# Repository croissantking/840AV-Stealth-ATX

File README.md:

$\color{#FF0000}{IMPORTANT!}$ <b>Working with switching power supplies involves dangerous, potentially lethal voltages, even when the device is disconnected from mains power. Improper handling can result in serious injury or death.

This repository provides Gerber files and related materials in good faith to the Macintosh hobby community, without any warranty or guarantee of any kind, including safety, reliability, or fitness for any particular purpose.

This design has not been safety-certified or fully validated under all operating conditions.

By using this material, you explicitly agree that:

- You assume all risk and responsibility for construction, modification, and use
- The author is not liable for any damage, injury, or death resulting from use or misuse
- You will only proceed if you are qualified and understand high-voltage electronics safety

If you are not experienced with mains-powered or high-voltage electronics, do not attempt to use this material.</b>

<b>Introduction and Outline</b>
-
This two-layer 'ATX Conversion Board' PCB enables you rebuild a failed Delta SMP-220DB Power Supply, found in your Apple Macintosh Quadra 800/840AV or Power Macintosh 8100, with easily obtainable second hand parts.

The PCB replicates the exact dimensions of the Delta's lower PCB, securing to the chassis just as the original. It's designed to have the internals of one of the following Seasonic-based ATX power supplies stood off above it as a mezzanine board:

- Antec EarthWatts EA-380 / EA-430 / EA-500 (without 'D' suffix)
- Seasonic SS-350ET / SS-400ET / SS-500ET (ES suffix also OK)
- Seasonic S12-II 500W

The PCBs in these PSUs are all the same and are labelled ATX400W REV:A5. Some of the components may be slightly different based on the output rating.

If you want, you can modify the Gerbers to fit the mounting locations of your own chosen PSU. You can also drill holes into the board but note that a new connection should be made to the ground plane from each of the new standoff locations if doing this.

The design reuses the Delta SMP-220DB AC inlet board, and replicates both the original monitor passthrough power relay and fan speed control logic for authentic behaviour.

The 20/24 pin ATX harness is intended to be cut short and looped into the +12V, GND, -12V, +5V, PS_ON and +5VSB vias seen at the top of the new PCB. This is so a soft power inverter can be integrated, and also allows the original modular Mac PSU connector to be fitted in its original location.

BOM
-
Please see <a href="https://github.com/croissantking/840AV-Stealth-ATX/blob/main/BOM.csv" target="_blank" rel="noopener noreferrer">BOM.csv</a> for a parts list.

A Digikey cart is available here: https://www.digikey.co.uk/en/mylists/list/5MLRWHWYBX

Ordering
-
Simply download the Gerbers.zip file and then upload this to JLCPCB. Pick and Place files are available for the SMD parts, if desired.

Assembly
-
Here are the steps needed to assemble your rebuilt power supply. Note that I'm working with a slightly different pre-release board layout.

Once you have the bare Conversion Board PCB in your hands, decide if you'll be populating the fan circuit and the CRT relay as shown in the key above. Both circuits are optional. If you are not populating the fan control circuit then your fan should be connected to the ATX PCB. The through hole parts should be taken from the original Delta PSU (apart from the fan header), while SMDs should be newly obtained.

To install the AC inlet connector, either re-use the one from the original PSU or purchase a new one.

In this corner you'll install the 22-way MiniFit Jr Connector (you can bring this from the old board or purchase new), trimming off the mounting flange on one side in order to make way for a metal standoff. You'll also install a small capacitor and inverter for the soft power circuit.

Detach this little washer-type part from the original PCB and solder it here.

Now that the Conversion Board is populated you can fit the 4x standoffs. Place the ATX PCB on top and loosely screw it down with just the two standoffs marked '1' and '2' nearest the lower edge.

From the other side, you can start to trim the wires of your 20/24-pin ATX connector harness to the correct length to connect to the lower PCB. +12V, GND, -12V, +5V, PS_ON and +5VSB are needed; the rest can be shortened and insulated or desoldered as you wish. Hinge the ATX PCB upwards in order to get better access to solder.

You should cut back and insulate (or desolder) any drive connectors you don't need; the remaining ones will feed through the Delta housing circular cutout.

Here, all the connections have been successfully made, and the ATX PCB has been fully screwed down. 

Turn the assembly around again, and solder two short wires (live and neutral) from the Conversion Board to the ATX PCB. These should be at least 18AWG and preferably 16AWG.

The full assembly can now be installed in your Delta housing, and the AC inlet board plugged in to the Conversion Board.

$\color{#FF0000}{IMPORTANT!}$ The two large left-hand heatsinks on the ATX board have a high voltage when the unit is powered up (and for some time after power is disconnected) which will give you a nasty shock if you touch them. Please be extra careful.

Make sure to insulate the ferrite ring with kapton tape (or similar) so that it does not accidentally short out the exposed solder joints on the back of the inlet board.

You can re-use the original 120mm fan or install a modern replacement (e.g. Noctua). In my build I opted to re-use the original but it needed a longer cable with a three-pin connector for my Conversion Board's new header. So I peeled back the sticker over the motor to expose the solder points and replace the cable.

The cable was now long enough to reach the new header on the Conversion Board, with plenty of slack for ease of installation.

Here is the PSU fully assembled and ready to use.

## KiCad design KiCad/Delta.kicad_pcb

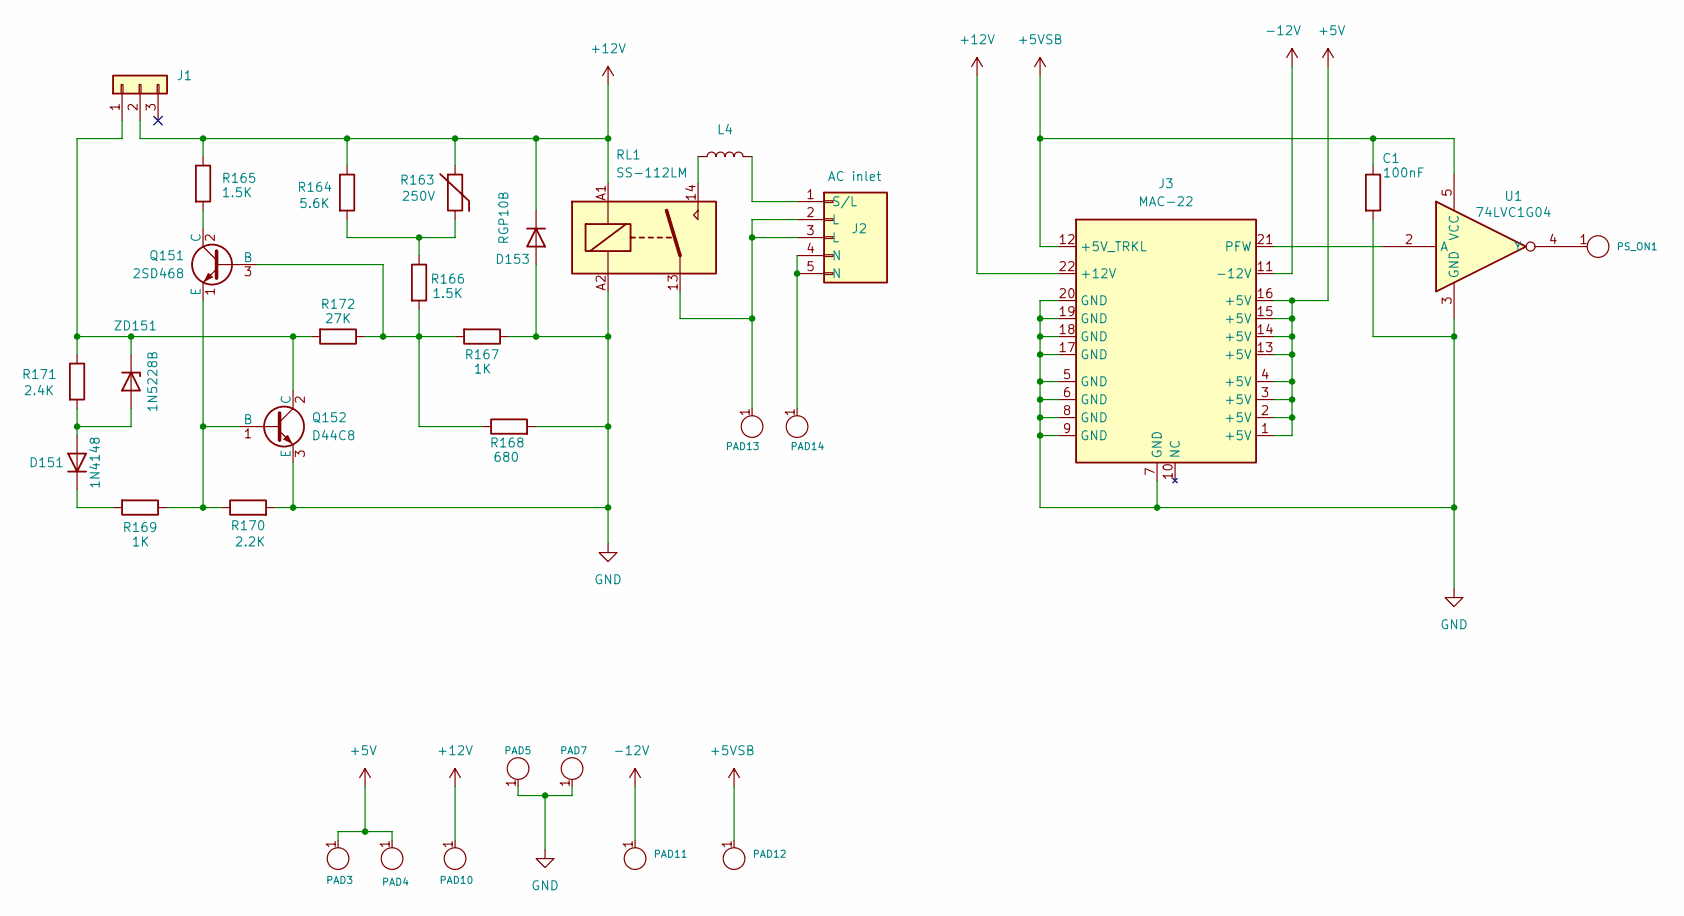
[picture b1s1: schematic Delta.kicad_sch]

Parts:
C1: 100nF; C_0805_2012Metric; LCSC C49678
D151: D_SOD-123; LCSC C83528
D153: D_DO-41_SOD81_P10.16mm_Horizontal
J1: Conn_01x03; FanPinHeader_1x03_P2.54mm_Vertical
J2: Conn_01x05; Pete_840AV_1x05_P4.00mm_Horizontal
J3: MAC-22; Molex_Mini-Fit_Jr_5569-22A1_2x11_P4.20mm_Horizontal_PETER
L4: L; L_Radial_L8.0mm_W8.0mm_P5.00mm_Neosid_SD8_PETER
PAD3, PAD4, PAD5, PAD7: SinglePad_PSU_Peter
PAD10: SinglePad_PSU_Peter_6_+12V
PAD11, PAD12: SinglePad_PSU_Peter_3_5VSB_-12V_PSON
PAD13, PAD14: SinglePad_PSU_Peter_1
PS_ON1: SinglePad_PSU_Peter_3_5VSB_-12V_PSON
Q151: 2SD468; TO-92_Inline_W4.0mm_Horizontal_FlatSideDown_PETER
Q152: D44C8; TO-220-3_Horizontal_TabDown
R163: 250V; RV_Disc_D7mm_W3.4mm_P5mm
R164: 5.6K; R_0805_2012Metric; LCSC C114538
R165, R166: 1.5K; R_0805_2012Metric; LCSC C114555
R167, R169: 1K; R_0805_2012Metric; LCSC C95781
R168: 680; R_0805_2012Metric; LCSC C93658
R170: 2.2K; R_0805_2012Metric; LCSC C114237
R171: 2.4K; R_0805_2012Metric; LCSC C114236
R172: 27K; R_0805_2012Metric; LCSC C114533
RL1: SS-112LM; Relay_SPST_Omron_G2RL-1A
U1: 74LVC1G04; SOT-23-5; LCSC C7827
ZD151: D_DO-35_SOD27_P10.16mm_Horizontal

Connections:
+5V: J3.1 (+5V), J3.2 (+5V), J3.3 (+5V), J3.4 (+5V), J3.13 (+5V), J3.14 (+5V), J3.15 (+5V), J3.16 (+5V), PAD3.1, PAD4.1
+5VSB: C1.1, J3.12 (+5V_TRKL), PAD12.1, U1.5 (VCC)
+12V: D153.1 (K), J1.2, J3.22 (+12V), PAD10.1, R163.1, R164.1, R165.1, RL1.A1
-12V: J3.11 (-12V), PAD11.1
GND: C1.2, D153.2 (A), J3.5 (GND), J3.6 (GND), J3.7 (GND), J3.8 (GND), J3.9 (GND), J3.17 (GND), J3.18 (GND), J3.19 (GND), J3.20 (GND), PAD5.1, PAD7.1, Q152.3 (E), R167.1, R168.2, R170.2, RL1.A2, U1.3 (GND)
unnamed: D151.2 (A), R171.2, ZD151.2 (A)
unnamed: D151.1 (K), R169.2
unnamed: J1.1, Q152.2 (C), R171.1, R172.2, ZD151.1 (K)
unnamed: J2.1 (CRT_L), L4.2
unnamed: J2.2 (L), J2.3 (L), PAD13.1, RL1.13
unnamed: J2.4 (N), J2.5 (N), PAD14.1
unnamed: J3.21 (PFW), U1.2 (A)
unnamed: L4.1, RL1.14
unnamed: Q151.3 (B), R166.2, R167.2, R168.1, R172.1
unnamed: Q151.2 (C), R165.2
unnamed: Q151.1 (E), Q152.1 (B), R169.1, R170.1
unnamed: R163.2, R164.2, R166.1
unnamed: PS_ON1.1, U1.4 (Y)

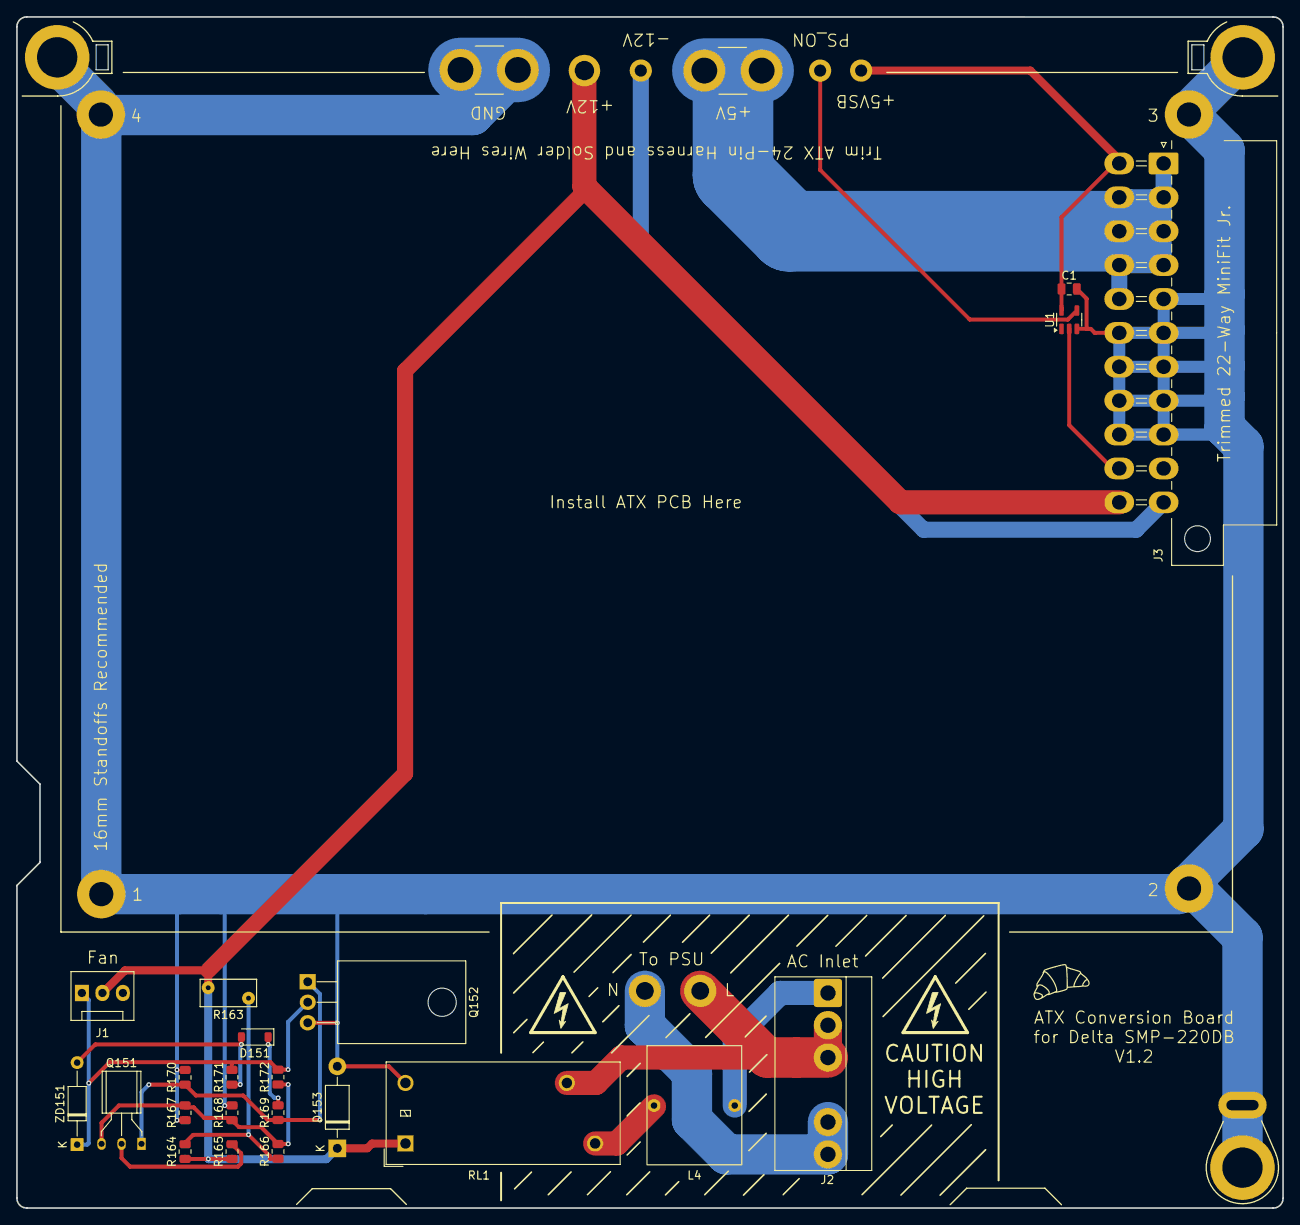
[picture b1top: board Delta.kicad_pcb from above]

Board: 2 copper layers, 156.9 x 147.6 mm, 32 parts (0 on the bottom side), 18 nets.

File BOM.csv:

"Item","Qty","Reference(s)","Value","Size (Imperial)","P/N","URL"
"Capacitor","1","C1","100nF","0805","CC0805KRX7R9BB104","https://www.digikey.co.uk/short/rhqt2bb8"
"Inverter","1","U1","74LVC1G04","SOT-23-5","SN74LVC1G04DBVR","https://www.digikey.co.uk/short/q94n5n4v"
"Varistor","1","R163","250V","","","Obsolete, reuse old part"
"Resistor","1","R164","5.6K","0805","RC0805FR-075K6L","https://www.digikey.co.uk/short/3hchtvn2"
"Resistor","2","R165, R166","1.5K","0805","RC0805FR-071K5L","https://www.digikey.co.uk/short/47733rr1"
"Resistor","2","R167, R169","1K","0805","RC0805FR-071KL","https://www.digikey.co.uk/short/3r7cmt8z"
"Resistor","1","R168","680","0805","RC0805JR-07680RL","https://www.digikey.co.uk/short/p1r5pjzt"
"Resistor","1","R170","2.2K","0805","RC0805JR-072K2L","https://www.digikey.co.uk/short/30m97n75"
"Resistor","1","R171","2.4K","0805","RC0805JR-072K4L","https://www.digikey.co.uk/short/4pn84b8b"
"Resistor","1","R172","27K","0805","RC0805FR-0727KL","https://www.digikey.co.uk/short/m2709928"
"Relay","1","RL1","OMIT-SS-112LM","","","Obsolete, reuse old part"
"Zener Diode","1","ZD151","1N5228B","DO-35","","https://www.digikey.co.uk/short/841nhv9d"
"Diode","1","D151","1N4148","SOD-123","1N4148W-7-F","https://www.digikey.co.uk/short/0tb77nc3"
"Diode","1","D153","RGP10B","DO-41","","https://www.digikey.co.uk/short/dnzptpbv"
"Transistor","1","Q151","2SD468","TO-92","","Obsolete, reuse old part"
"Transistor","1","Q152","D44C8","TO-220","","Obsolete, reuse old part"
"Connector","1","J1","Molex KK100, 6373","","22-23-2033","https://www.digikey.co.uk/short/rzfj2mbw"
"Connector","1","J2","Molex KK396, 5273","","09-65-2068","https://www.digikey.co.uk/short/9mqpdqwd"
"Connector","1","J3","Molex Mini-Fit Jr","","39-29-1227","https://www.digikey.co.uk/short/t949vm2z"
"Inductor","1","L4","","","","Obsolete, reuse old part"

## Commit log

2026-04-27 Create jdaksld
2026-04-27 Create sjklafdjsdklf
2026-04-27 OKAY
2026-04-27 Update README.md
    Added PCB render
2026-05-14 Add files via upload
    Small adjustments to silkscreen for final release. I am still calling this V1.1.
2026-05-14 Add files via upload
    Edited these files to remove designators that aren't needed - we only need to place SMD parts.
2026-05-14 Add files via upload
    Small silkscreen tweaks ahead of initial release.
2026-05-14 Rename Front.png to Preview/Front.png
2026-05-14 Rename Back.png to Preview/Back.png
2026-05-14 Rename Delta-symbols.kicad_sym to KiCad/Delta-symbols.kicad_sym
2026-05-14 Rename Delta.kicad_pcb to KiCad/Delta.kicad_pcb
2026-05-14 Rename Delta.kicad_pro to KiCad/Delta.kicad_pro
2026-05-14 Rename Delta.kicad_sch to KiCad/Delta.kicad_sch
2026-05-14 Rename fp-lib-table to KiCad/fp-lib-table
2026-05-14 Rename sym-lib-table to KiCad/sym-lib-table
2026-05-14 Rename KiCad/C_0805_2012Metric.kicad_mod to KiCad/Delta-footprints.pretty/C_0805_2012Metric.kicad_mod
2026-05-14 Create LICENSE
2026-05-14 Add files via upload
    Version 1.2 of the gerbers focuses on some changes to safety - layout and warnings have been improved
2026-05-14 Add files via upload
    V1.2
